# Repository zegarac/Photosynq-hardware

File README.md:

Photosynq-hardware
==================

Photosynq KiCad files for the main board and other associated hardware.  

Handheld unit is the photosynq board for the handheld photosynq device.  The libraries required are located in the zipped library document, as well as in the main folder itself.  Unzip them and direct KiCad to those locations when specifying additional library locations.

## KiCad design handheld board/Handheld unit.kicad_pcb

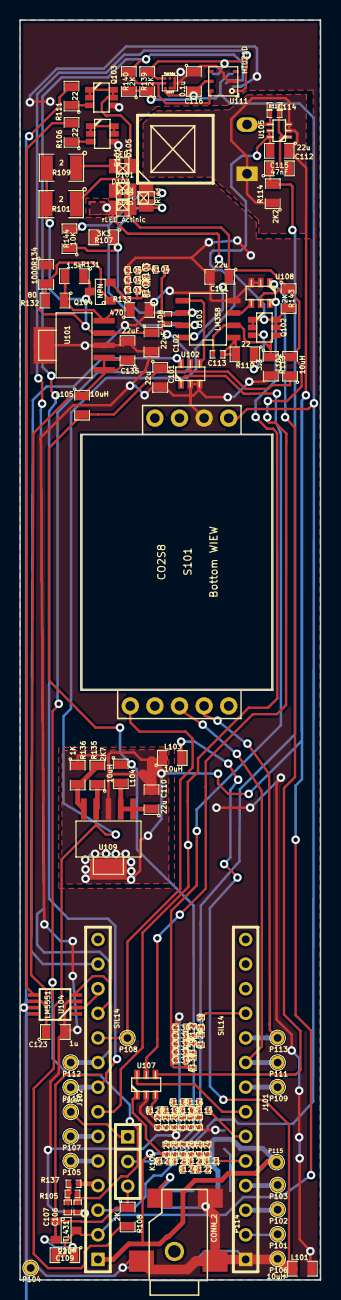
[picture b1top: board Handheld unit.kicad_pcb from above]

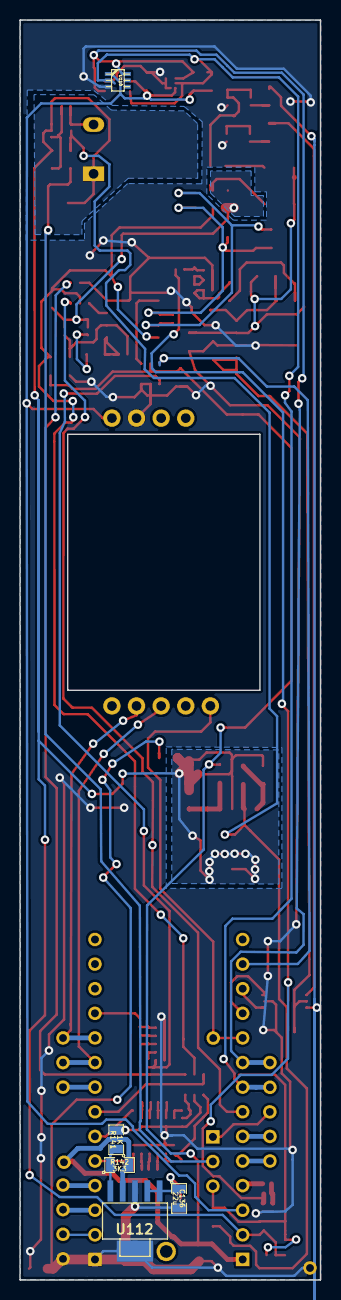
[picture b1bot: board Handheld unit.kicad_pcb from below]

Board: 2 copper layers, 31.0 x 130.0 mm, 127 parts (5 on the bottom side), 79 nets.

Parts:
C101, C109, C110, C111, C112, C136: 22u; SM0805
C102, C135: 22uF; SM0805
C103, C104, C105, C106, C107, C117, C118, C119, C120, C121, C122, C124, C125, C126, C127, C128, C129, C130, C131, C132, C133, C134: 10n; SM0402
C108, C113: 100p; SM0402
C114: 10p; SM0402
C115: 47nF; SM0805
C116: 0.1u; SM0805
C123: 1u; SM0805
D101, D103: LED; Luxeon_Z+
D102: IRled; Luxeon_Z+
D104: rLED_Actinic; Luxeon_Z+
D105: SMALL_DIODE_PHOTODIODE; Pin_diode_SIP_down
J101, J102: SIL14; SIL-14
K101: CONN_3; SIL-3
L101, L102, L103, L104, L105: 10uH; SM0805
P101, P102, P103, P104, P105, P106, P107, P108, P109, P110, P111, P112, P113, P115, P116: CONN_1; 1pins
P114: CONN_2; power_barrel_S
Q101, Q102, Q103: MOSN-TSOP6; TSOP-6
Q104: NPN; SOT23
R101, R109: 2; SM1210
R102, R103, R104, R105, R115, R116, R117, R118, R119, R120, R121, R122, R123, R124, R125, R126, R127, R128, R129, R130, R137, R138: 3.3K; SM0402
R106, R110, R111: 22; SM0805
R107, R142: 3K3; SM0805
R108, R139, R140, R143: 2K; SM0805
R112: 27K; SM0402
R113: 3.3; SM0805
R114: 2K2; SM0805
R131: 1.5k; SM0805
R132: 80; SM0805
R133: 470; SM0805
R134: 1000; SM0805
R135: 2K7; SM0805
R136, R141: 1K; SM0805
R144: 10K; SM0805
S101: CO2S8
U101, U109, U112: TL1963; DCQ5
U102, U107, U108: DG4157DL-T1-E3; sot23-6
U103: LM358; SO8E
U104: LM5551; MSOP_8
U105: LMH6601; sc70-6
U106: TL431; SOT23
U110: TCS3471; sc70-6
U111: HTU21D; dfn6
U113: TMP006; WCSP-8

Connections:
/3.3Vdd: C116.2, J102.3, R139.1, R140.1, S101.1, U110.1, U111.5, U113.a3
/+5V: C101.1, J102.1, L102.1, L104.1, L105.2, P115.1, R142.2, U102.5, U112.4
/ACT_SAT-LED: D104.2, Q102.1, Q102.2, Q102.5, Q102.6, R143.2
/ACT_SAT_FB: C113.2, Q102.4, R113.1, U103.2
/ActVCC: C111.1, D104.1, L102.2, R143.1, U103.8, U107.5, U108.5
/Ain10: C115.1, K101.2, R114.2
/Ain11: K101.1, P116.1
/Aref: C109.1, K101.3, R108.1, U106.1, U106.2
/DGND: L101.1, L103.2
/DetVcc: C112.2, R108.2, R135.1, U105.5, U105.6, U109.4
/Det_gnd: C109.2, C110.2, C112.1, D105.1, J102.2, L103.1, R114.1, R136.1, U105.2, U105.3, U106.3, U109.3
/IR CAL toggle: J102.13, U102.6
/IR_CAL_filtered: C134.1, R130.2, U102.1
/PWM meas intensity: J102.4, R137.2
/PWM_calibration_intensity: J101.11, R138.1
/PWMactpreset1: J101.6, R115.1
/PWMactpreset2: J101.5, R121.1
/Rxd: J101.9, P111.1, S101.7
/Txd: J101.10, P113.1, S101.8
/Umeas1: J102.12, U104.2
/Umeas2: J102.11, U104.4
/actinic_filtered&switched: U103.3, U108.4
/actinic_preset1: C122.1, R120.2, U107.3
/actinic_preset2: C129.1, R126.2, U107.1
/cal: J102.10, P108.1, S101.5
/calibration_LED: C108.1, D102.1, R144.2, U103.7
/pinK: C114.1, D105.2, R112.1, U105.4
/preselected ACT: U107.4, U108.1
/sck: J102.8, P110.1, R140.2, U110.2, U111.6, U113.b3
/sda: J102.9, P112.1, R139.2, U110.6, U111.1, U113.c3
/signal: C114.2, C115.2, R112.2, U105.1
/toggle act1/act2: J101.7, U107.6
/toggle act ON/OFF: J102.7, U108.6
GND: C101.2, C102.2, C103.2, C104.2, C105.2, C106.2, C107.2, C111.2, C116.1, C117.2, C118.2, C119.2, C120.2, C121.2, C122.2, C123.2, C124.2, C125.2, C126.2, C127.2, C128.2, C129.2, C130.2, C131.2, C132.2, C133.2, C134.2, C135.2, C136.2, J101.1, L101.2, P104.1, P106.1, P114.2, Q101.4, Q103.4, R107.2, R113.2, R133.2, R134.1, R141.2, S101.2, U101.3, U102.2, U102.3, U103.4, U104.3, U107.2, U108.2, U108.3, U110.3, U111.2, U112.3, U113.a1, U113.a2, U113.b1, U113.c1
unnamed: U102.4, U103.5
unnamed: R131.2, R132.1, R133.1, U101.5
unnamed: J102.5, P105.1
unnamed: J101.2, P101.1
unnamed: J101.4, P103.1
unnamed: J101.8, P109.1
unnamed: J102.6, P107.1
unnamed: D103.2, Q103.1, Q103.2, Q103.5, Q103.6
unnamed: Q104.1, R132.2, R134.2
unnamed: R135.2, R136.2, U109.5
unnamed: D103.1, R109.1
unnamed: D101.1, R101.1
unnamed: Q101.3, R106.1
unnamed: Q103.3, R111.1
unnamed: R106.2, U104.5
unnamed: R141.1, R142.1, U112.5
unnamed: C136.1, U112.1, U112.2
unnamed: D101.2, Q101.1, Q101.2, Q101.5, Q101.6
unnamed: R111.2, U104.7
unnamed: J101.3, P102.1
unnamed: C123.1, C135.1, L105.1, U101.1, U101.2, U104.6
unnamed: C133.1, R129.2, R130.1
unnamed: C108.2, D102.2, R107.1, R144.1, U103.6
unnamed: C130.1, R127.1, R138.2
unnamed: C131.1, R127.2, R128.1
unnamed: C132.1, R128.2, R129.1
unnamed: C102.1, Q104.3, R101.2, R109.2, R131.1, U101.4
unnamed: C103.1, Q104.2, R102.1
unnamed: C104.1, R102.2, R103.1
unnamed: C105.1, R103.2, R104.1
unnamed: C106.1, R104.2, R105.1
unnamed: C107.1, R105.2, R137.1
unnamed: C120.1, R118.2, R119.1
unnamed: C118.1, R116.2, R117.1
unnamed: C119.1, R117.2, R118.1
unnamed: C117.1, R115.2, R116.1
unnamed: C121.1, R119.2, R120.1
unnamed: C124.1, R121.2, R122.1
unnamed: C125.1, R122.2, R123.1
unnamed: C126.1, R123.2, R124.1
unnamed: Q102.3, R110.1
unnamed: C113.1, R110.2, U103.1
unnamed: C127.1, R124.2, R125.1
unnamed: C128.1, R125.2, R126.1
unnamed: C110.1, L104.2, U109.1, U109.2

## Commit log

2013-10-07 Added current KiCad Libraries needed for board, zipped.
2013-10-07 deleted component file tc4427.lib
    Because we do not use this component in the design, we use LM5551
    instead
